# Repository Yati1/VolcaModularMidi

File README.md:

# VolcaModularMidi

The [original Volca midi project](https://github.com/sensai7/VolcaModularMidi) seemed to have a glitch where after a few seconds of playing the volca will get stuck on a single-note. After some investigating I found that [this way of wiring up the octocoupler fixed the issue](https://hackaday.com/tag/6n137/). 

This is a hardware mod to add MIDI IN capability to the [Korg Volca Modular](https://www.korg.com/us/products/dj/volca_modular/)

## Schematic

## Bill Of Materials:
 * R1  220 ohm resistor
 * R2  270 ohm resistor
 * D1  1N4148 diode
 * J1  2.54mm header
 * J2  DIN-5 connector
 * U1  6n139 optocoupler (6n138 and 6n137 should also work as well)

## How to install:

BEFORE YOU BEGIN: 

* This installation process requires you to open your Korg volca Modular, most likely voiding the warranty. The creator of this mod and all the contributors of this project are not to be held responsible for possible malfunctions caused by this process.

* In these example photos the mod was already installed (the red/orange/yellow/green cables), but I repeated the process to take the photos and make it easier to explain.

* Read the tutorial and make sure you understand all the steps before proceeding.

Be sure to have the following tools:
  * M3 screwdriver
  * Flat screwdriver (not absolutely necessary but it's useful to unplug the ribbon connectors)
  * Pliers or something to snip and cut thin cables
  * A dril or any tool to open a hole in the case

1-	Unscrew the screws from the back.

2-	Gently pull from a potentiometer to detach the blue case from the circuit.

3-	Unplug the batteries connector (red/black cables) in the top right of the board

4-	Lay the circuit down, be careful with the speaker connection (orange/brown cables)

5-	You can see the holes now, they're labelled as MIDI_RX, MIDI_TX, +3.3V, GND

6-	Unpeel the black tape and unplug the keyboard connector (white/orange cables)

7-	Unscrew the 6 screws attaching the main board with the keyboard board.

8-	Sit the main board on it's place in the blue case and open a hole on the right side enough to let the four cables go through. Then solder the four cables facing down and snip the excess wire. (disregard the quality of mine, I don't have the tools nor skill for these things :( )

9-	Repeat the process from steps 7 to 1 in inverse order to reassemble the unit.

## Mod mods

If you have the tools, and patience, you can glue the female connections to the case so you can plug it directly (here's a poorly photoshopped concept illustrating it)

If you prefer to use a 3.5mm stereo jack instead of the big DIN-5 connector, here's another poorly photoshopped concept

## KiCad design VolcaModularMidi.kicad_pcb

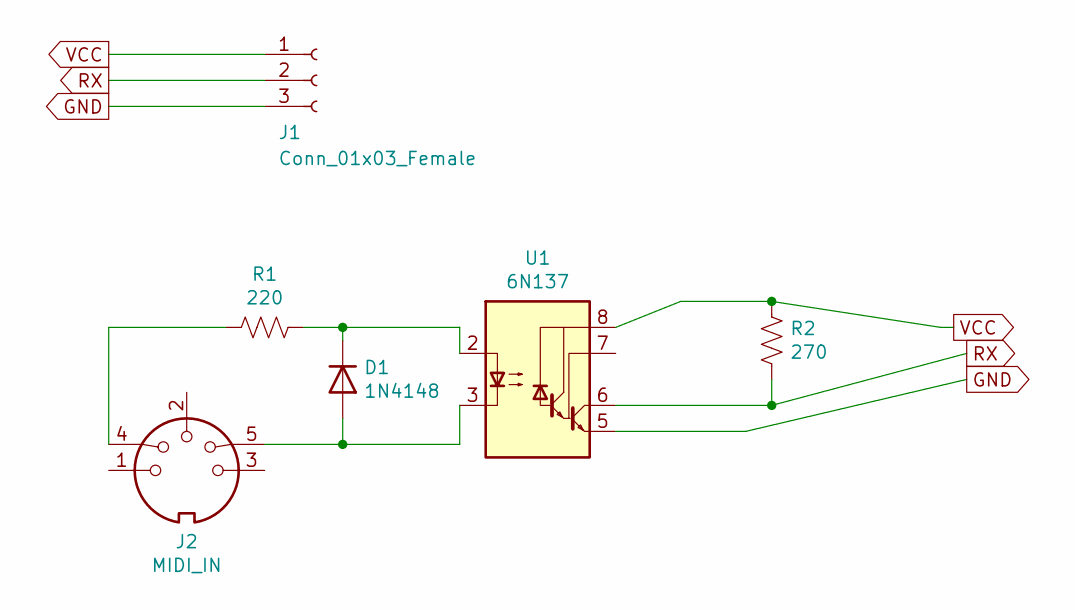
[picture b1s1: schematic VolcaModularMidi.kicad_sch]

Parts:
D1: 1N4148; D_DO-35_SOD27_P7.62mm_Horizontal
J1: Conn_01x03_Female; JST_EH_B3B-EH-A_1x03_P2.50mm_Vertical
J2: MIDI_IN; MIDI_DIN5
R1: 220; R_Axial_DIN0207_L6.3mm_D2.5mm_P7.62mm_Horizontal
R2: 270; R_Axial_DIN0207_L6.3mm_D2.5mm_P7.62mm_Horizontal
U1: 6N137; DIP-8_W7.62mm_LongPads

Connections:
GND: J1.3, U1.5 (GND)
unnamed: D1.1 (K), R1.1, U1.2 (C1)
unnamed: D1.2 (A), J2.5, U1.3 (C2)
unnamed: J2.4, R1.2
RX: J1.2, R2.2, U1.6 (VO2)
VCC: J1.1, R2.1, U1.8 (VCC)

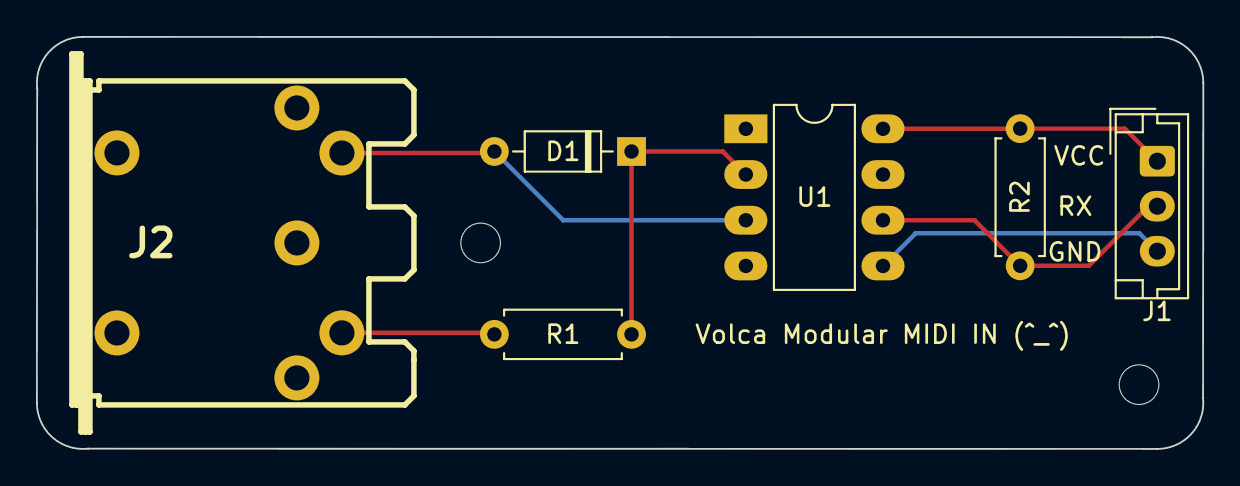
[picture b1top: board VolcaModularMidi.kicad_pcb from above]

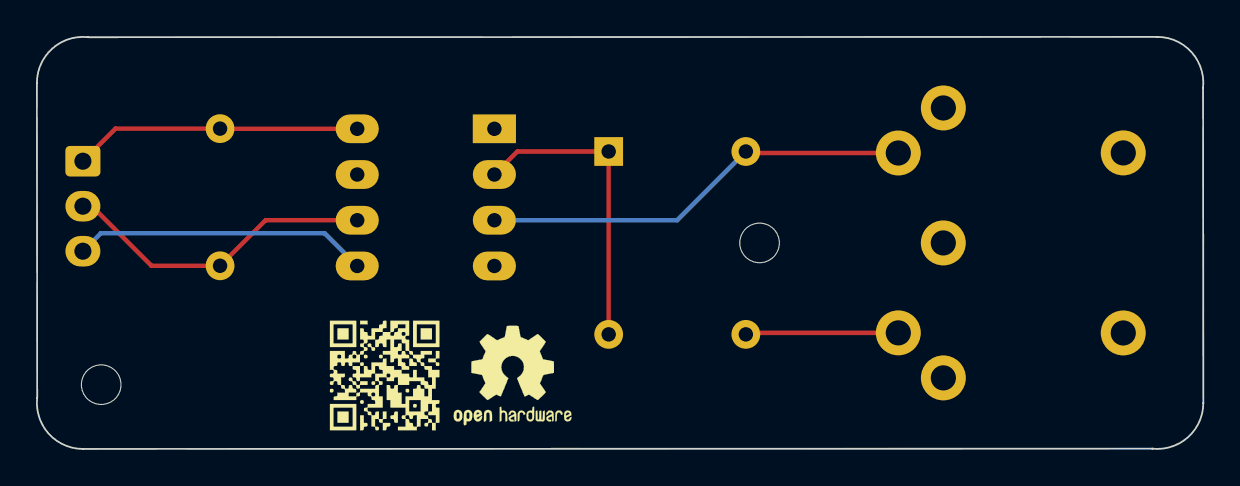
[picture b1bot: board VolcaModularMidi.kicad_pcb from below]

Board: 2 copper layers, 64.8 x 22.9 mm, 8 parts (2 on the bottom side), 6 nets.

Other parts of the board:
 : volcaMidiProjUrl
 #2: OSHW-Logo2_7.3x6mm_SilkScreen

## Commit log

2022-02-08 Edited schematic with my fix
2022-02-10 Finished routing and laying out pcb
2022-02-10 Updated gitignore
2022-02-11 Deleting old project files
2022-02-11 Added mounting holes, replaced jumper connector with jst connector
2022-02-11 Added URL QR code
2022-02-11 Generated gerbers and drill files
